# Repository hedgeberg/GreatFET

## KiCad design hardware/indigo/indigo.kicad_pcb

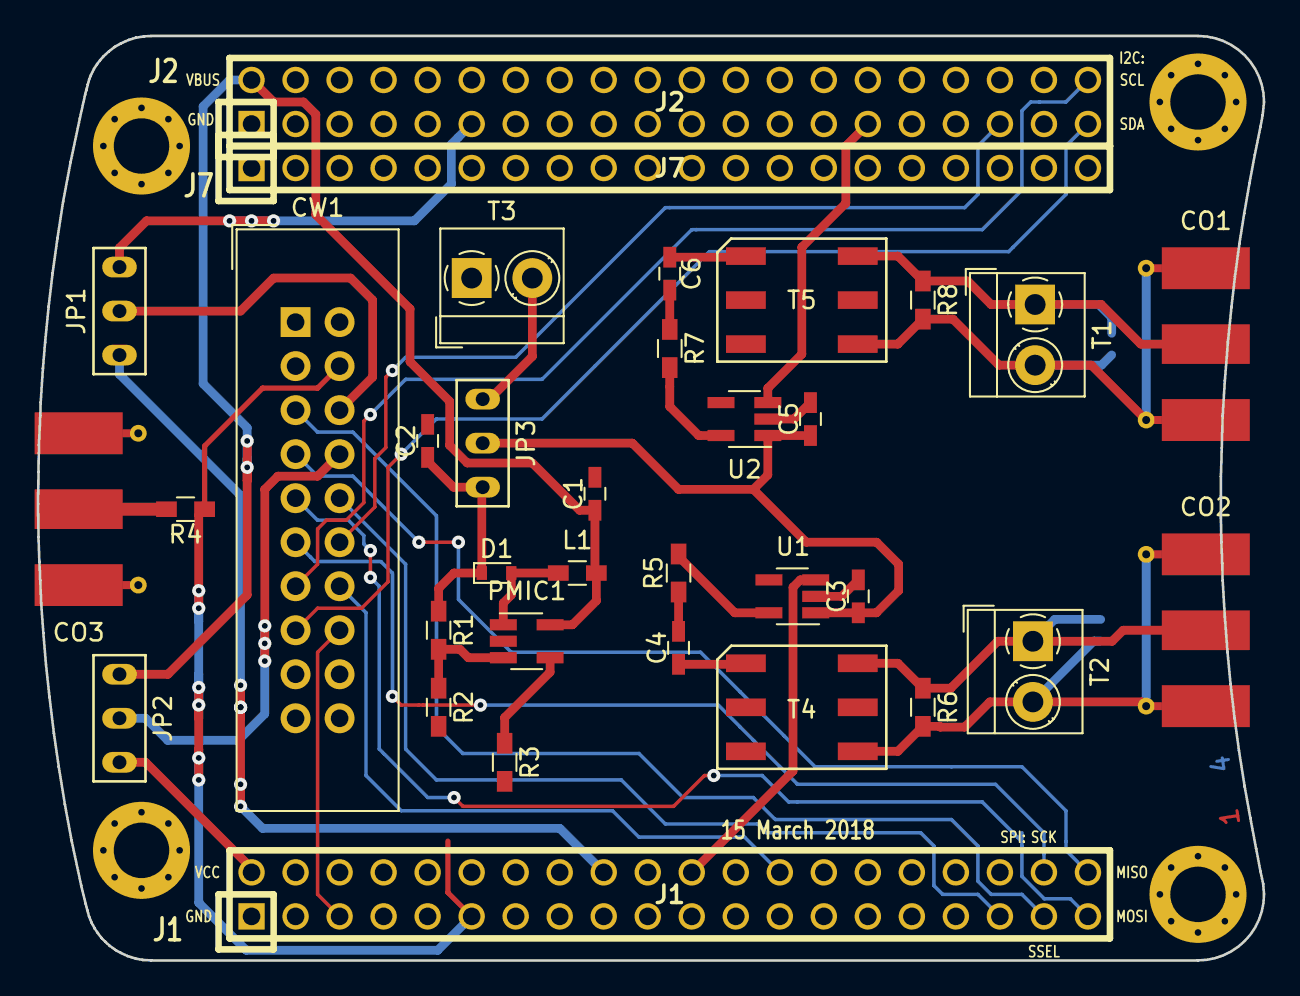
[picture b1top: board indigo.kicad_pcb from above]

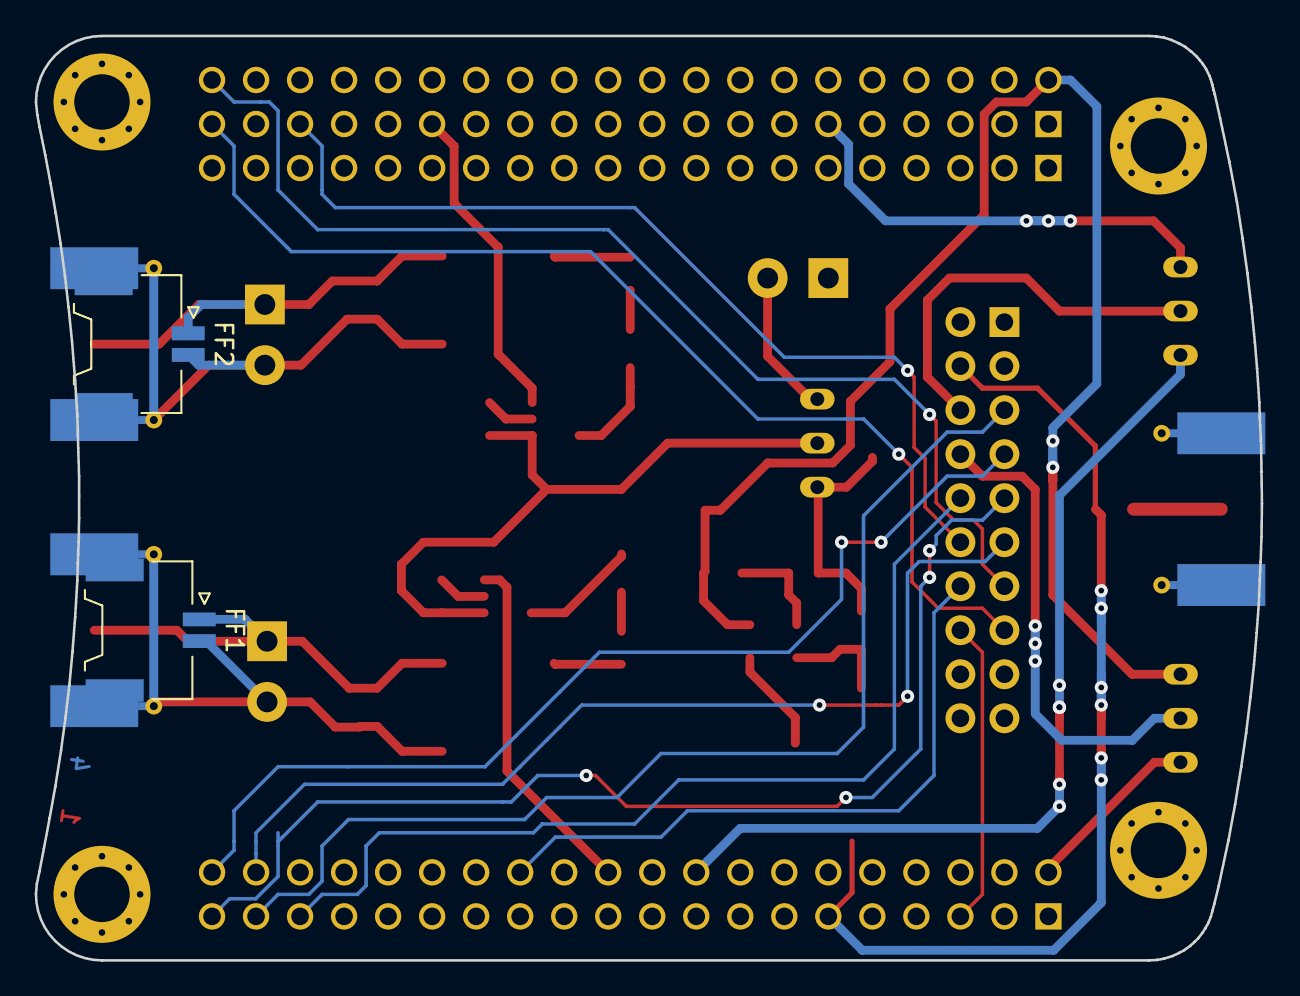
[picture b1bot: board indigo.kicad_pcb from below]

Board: 4 copper layers, 70.7 x 53.3 mm, 40 parts (2 on the bottom side), 35 nets.

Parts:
C1, C2, C3, C4, C5, C6: C; C_0603_HandSoldering
CO1, CO2, CO3: Conn_Coaxial; Molex_SMA_Jack_Edge_Mount
CW1: CW-HEADER; IDC-Header_2x10_Pitch2.54mm_Straight
D1: D; D_0603
FF1, FF2: Conn_01x02; Molex_Panelmate-53780-0270_02x1.25mm_Angled
J1: NEIGHBOR1; HEADER-2x20
J2: NEIGHBOR2; HEADER-2x20
J7: BONUS_ROW; HEADER-1x20
JP1, JP2, JP3: Jumper_NC_Dual; JUMP3
L1: L; L_0603_HandSoldering
MH1, MH2, MH3, MH4: MOUNTING_HOLE; HOLE126MIL-COPPER
PMIC1: AP3012; SOT-23-5_HandSoldering
R1, R2, R3, R6, R8: R; R_0603_HandSoldering
R4: 50R; R_0603_HandSoldering
R5, R7: R-SHORTED; R_0603_HandSoldering
T1, T2, T3: Screw_Terminal_01x02; TerminalBlock_MetzConnect_Type059_RT06302HBWC_Pitch3.50mm
T4, T5: BALUN
U1, U2: UCC2751X-SOT23-5; SOT-23-5_HandSoldering

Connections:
/CW_CLKIN: CW1.4, J1.11, R4.1
/CW_TRIGGER: CW1.16, J1.5
/CW_VREF: CW1.8, JP2.2
/GATE_DRIVE_SEQ1: J1.22, U1.3
/GATE_DRIVE_SEQ2: J2.29, U2.3
/GF_CLKIN: J2.11, JP1.1
/GF_GPIO1: CW1.14, J1.26
/GF_I2C_CLK: CW1.13, J2.40
/GF_I2C_DAT: CW1.15, J2.39
/GF_MISO: CW1.7, J1.40
/GF_MOSI: CW1.9, J1.39
/GF_SCK: CW1.11, J1.38
/GF_SSEL: CW1.5, J1.37
/GF_UART_RX: CW1.12, J2.35
/GF_UART_TX: CW1.10, J1.35
/GLITCH_GEN: J1.18, JP1.3
/GLITCH_OR_CLKOUT: CW1.6, JP1.2
/Glitch Driver/DRIVE+: CO1.1, CO2.1, FF1.1, FF2.1, R6.1, R8.1, T1.1, T2.1, T4.6, T5.6
/Glitch Driver/DRIVE-: CO1.2, CO2.2, FF1.2, FF2.2, R6.2, R8.2, T1.2, T2.2, T4.4, T5.4
/Glitch Driver/V_GATEDRIVE: C3.1, C5.1, JP3.2, U1.1, U2.1
/V_DRIVE_BOOST: C2.1, D1.1, JP3.1, R1.1
GND: C1.2, C2.2, C3.2, C5.2, CO3.2, CW1.2, CW1.17, CW1.19, J1.1, J2.1, J7.1, J7.10, J7.19, MH1.1, MH2.1, MH3.1, MH4.1, PMIC1.2, R2.2, R3.2, T3.1, T4.3, T5.3, U1.2, U1.4, U2.2, U2.4
unnamed: C4.1, T4.1
unnamed: C4.2, R5.1
unnamed: C6.1, T5.1
unnamed: C6.2, R7.1
unnamed: CO3.1, R4.2
unnamed: D1.2, L1.1, PMIC1.1
unnamed: JP3.3, T3.2
unnamed: PMIC1.3, R1.2, R2.1
unnamed: PMIC1.4, R3.1
unnamed: R5.2, U1.5
unnamed: R7.2, U2.5
VBUS: C1.1, J2.2, JP2.3, L1.2, PMIC1.5
VCC: J1.2, J7.20, JP2.1

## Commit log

2018-02-14 USB host: improve tracking of USB endpoints
2018-03-15 Mapped connectors and did initial routing for Indigo
